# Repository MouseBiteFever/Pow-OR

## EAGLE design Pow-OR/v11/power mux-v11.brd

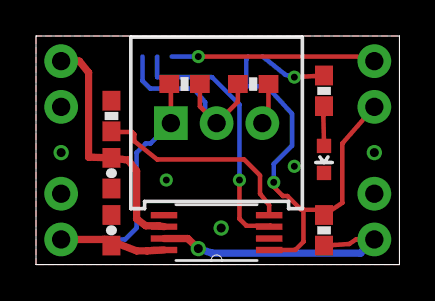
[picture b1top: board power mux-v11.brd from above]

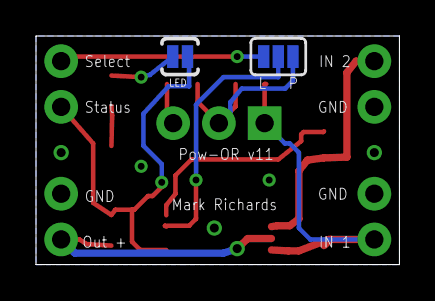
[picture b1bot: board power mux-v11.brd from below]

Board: 2 copper layers, 20.2 x 12.7 mm, 16 parts (2 on the bottom side), 11 nets.

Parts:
C1, C2: 1uf; 0603-CAP
D1: GREEN; LED-0603
JP3, JP4, JP5, JP6: M021X02_NO_SILK; 1X02_NO_SILK
R1: TRIMPOT-PTH-KNOB; 3386U
R2, R3: 0603-RES
R5: 400; 0603-RES
R6: 4.7k; 0603-RES
R7: 180; 0603-RES
SJ1: SJ_3_PASTE1&2
SJ2: SOLDERJUMPERNC2; SJ_2S-NOTRACE
U1: TPS2113APWR; SOP65P640X120-8N

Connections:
GND: C1.1, C2.2, D1.C, JP3.1, JP4.1, JP6.1, R1.3, R2.2, R5.1, U1.2, U1.5
ILIM: R5.2, U1.4
IN1: C1.2, JP3.2, R1.1, R3.1, U1.8
IN2: C2.1, JP4.2, U1.6
unnamed: D1.A, R7.2
unnamed: R1.2, R2.1, R3.2, SJ1.1
unnamed: R7.1, SJ2.1
OUT: JP6.2, R6.1, U1.7
SELECT: JP5.2, SJ1.3
STAT: JP5.1, R6.2, SJ2.2, U1.1
VSENS: SJ1.2, U1.3

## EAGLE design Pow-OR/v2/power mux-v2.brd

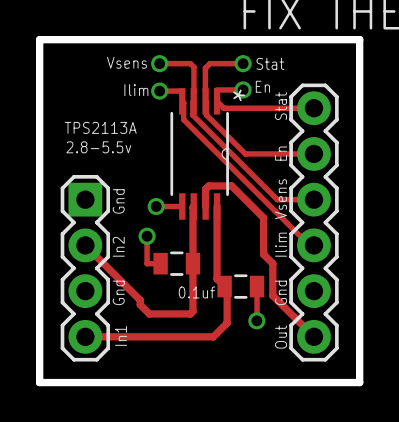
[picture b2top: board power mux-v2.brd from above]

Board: 2 copper layers, 17.8 x 19.1 mm, 5 parts (0 on the bottom side), 8 nets.

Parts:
C1, C2: 0805
JP2: 1X04
JP3: 1X06
U1: TPS2113APWR; SOP65P640X120-8N

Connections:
EN: JP3.5, U1.2
GND: C1.2, C2.2, JP2.1, JP2.3, JP3.2, U1.5
ILIM: JP3.3, U1.4
IN1: C1.1, JP2.4, U1.8
IN2: C2.1, JP2.2, U1.6
OUT: JP3.1, U1.7
STAT: JP3.6, U1.1
VSENS: JP3.4, U1.3

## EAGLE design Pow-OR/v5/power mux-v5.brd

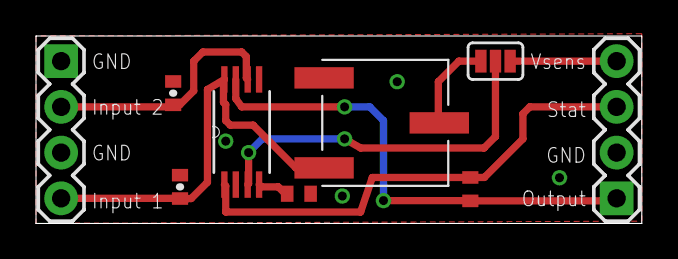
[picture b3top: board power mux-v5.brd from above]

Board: 2 copper layers, 33.7 x 10.4 mm, 9 parts (0 on the bottom side), 9 nets.

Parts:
C3, C4: 1uf; 0402-CAP
JP1, JP2: 1X04
R2: 400; R0402
R3: 4.7k; R0402
SJ1: SJ_3_PASTE1&2
U1: TPS2113APWR; SOP65P640X120-8N
U$2: TRIMPOT-10K

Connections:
GND: C3.2, C4.1, JP1.2, JP2.1, JP2.3, R2.1, U1.2, U1.5, U$2.1
ILIM: R2.2, U1.4
IN1: C4.2, JP2.4, U1.8, U$2.2
IN2: C3.1, JP2.2, U1.6
unnamed: SJ1.1, U$2.3
OUT: JP1.1, R3.1, U1.7
SELECT: JP1.4, SJ1.3
STAT: JP1.3, R3.2, U1.1
VSENS: SJ1.2, U1.3

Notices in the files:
parts and their libraries:
SparkFun-Connectors: Licensing: CC v3.0 Share-Alike You are welcome to use this library for commercial purposes.
